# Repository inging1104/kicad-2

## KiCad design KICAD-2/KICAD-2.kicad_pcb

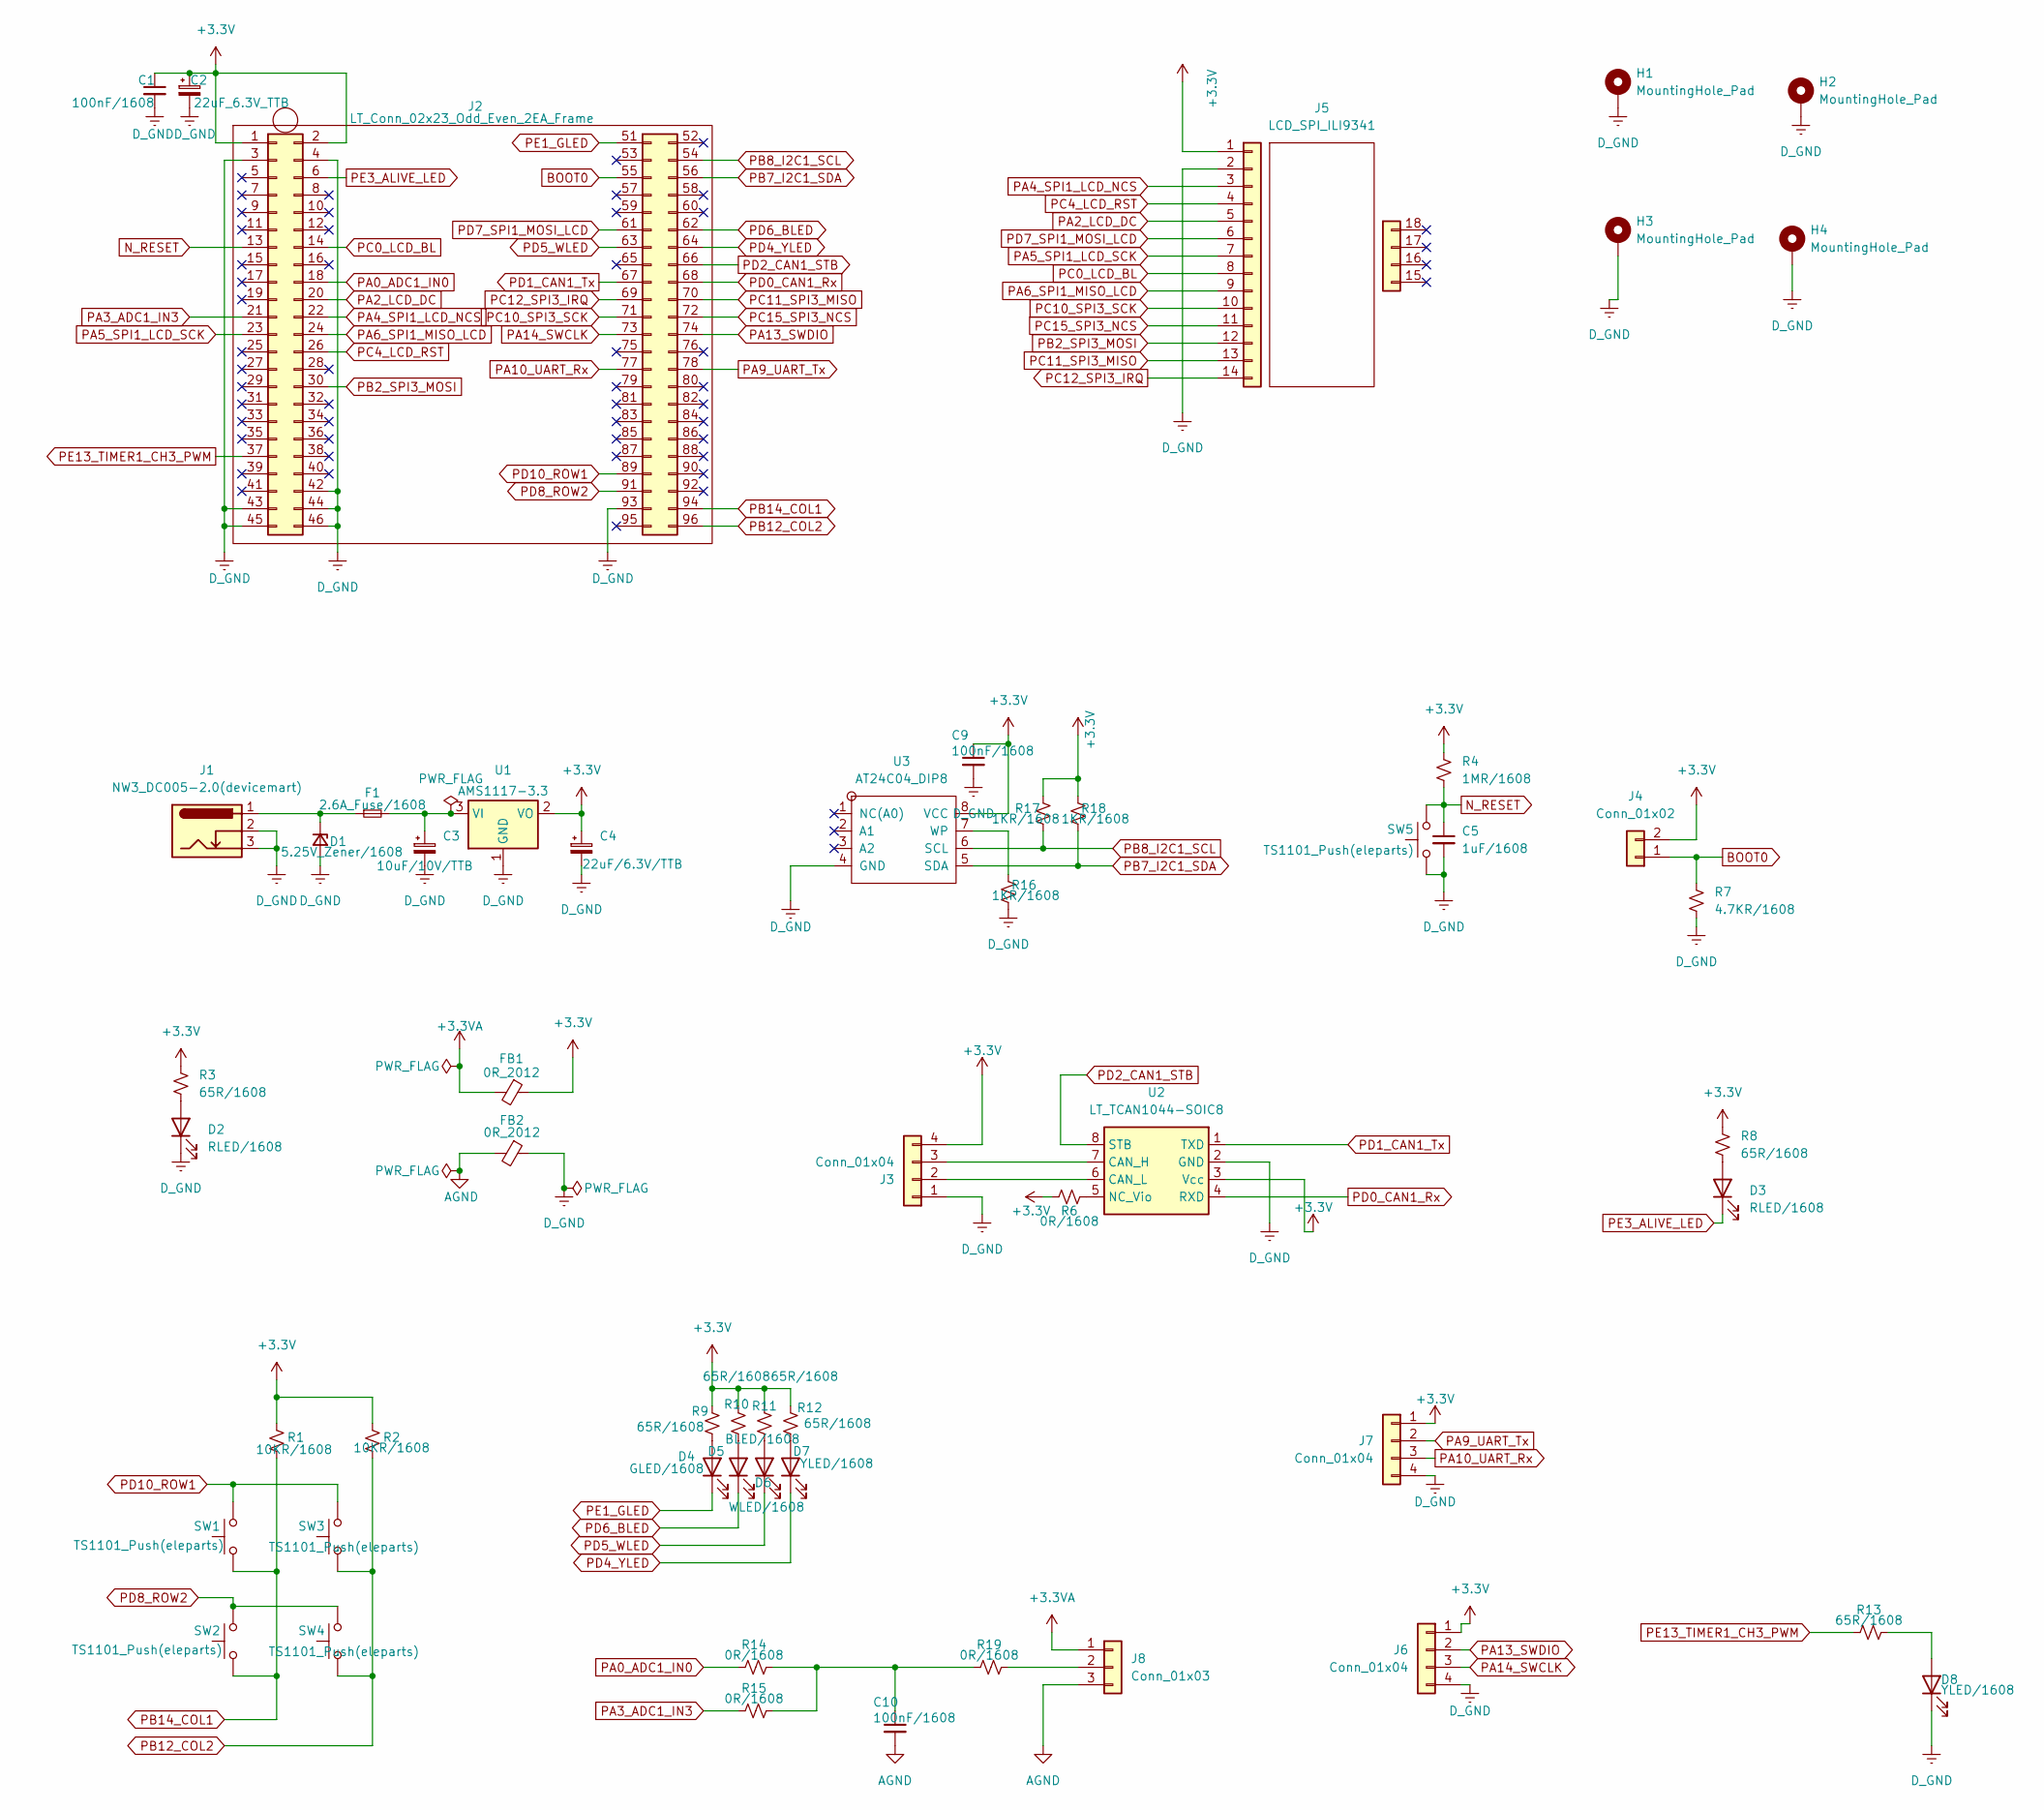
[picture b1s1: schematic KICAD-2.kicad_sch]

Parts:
C1, C9, C10: 100nF/1608; C_0603_1608Metric_Pad1.08x0.95mm_HandSolder
C2: 22uF_6.3V_TTB; CP_EIA-3528-21_Kemet-B_Pad1.50x2.35mm_HandSolder
C3: 10uF/10V/TTB; CP_EIA-3528-21_Kemet-B_Pad1.50x2.35mm_HandSolder
C4: 22uF/6.3V/TTB; CP_EIA-3528-21_Kemet-B_Pad1.50x2.35mm_HandSolder
C5: 1uF/1608; C_0603_1608Metric_Pad1.08x0.95mm_HandSolder
D1: 5.25V_Zener/1608; D_0603_1608Metric_Pad1.05x0.95mm_HandSolder
D2, D3: RLED/1608; LED_0603_1608Metric_Pad1.05x0.95mm_HandSolder
D4: GLED/1608; LED_0603_1608Metric_Pad1.05x0.95mm_HandSolder
D5: BLED/1608; LED_0603_1608Metric_Pad1.05x0.95mm_HandSolder
D6: WLED/1608; LED_0603_1608Metric_Pad1.05x0.95mm_HandSolder
D7, D8: YLED/1608; LED_0603_1608Metric_Pad1.05x0.95mm_HandSolder
F1: 2.6A_Fuse/1608; Fuse_0603_1608Metric_Pad1.05x0.95mm_HandSolder
FB1, FB2: 0R_2012; R_0805_2012Metric_Pad1.20x1.40mm_HandSolder
H1, H2, H3, H4: MountingHole_Pad; LT_MountingHole_3.2mm_M3_Pad_TopBottom
J1: NW3_DC005-2.0(devicemart); BarrelJack_GCT_DCJ200-10-A_Horizontal
J2: LT_Conn_02x23_Odd_Even_2EA_Frame; LT_STM32F767VGT-23x2_Frame
J3, J6, J7: Conn_01x04; PinHeader_1x04_P2.54mm_Vertical
J4: Conn_01x02; PinHeader_1x02_P2.54mm_Vertical
J5: LCD_SPI_ILI9341; LT_LCD_SPI_ILI9341_P2.54mm
J8: Conn_01x03; PinHeader_1x03_P2.54mm_Vertical
R1, R2: 10KR/1608; R_0603_1608Metric_Pad0.98x0.95mm_HandSolder
R3, R8, R9, R10, R11, R12, R13: 65R/1608; R_0603_1608Metric_Pad0.98x0.95mm_HandSolder
R4: 1MR/1608; R_0603_1608Metric_Pad0.98x0.95mm_HandSolder
R6, R14, R15, R19: 0R/1608; R_0603_1608Metric_Pad0.98x0.95mm_HandSolder
R7: 4.7KR/1608; R_0603_1608Metric_Pad0.98x0.95mm_HandSolder
R16, R17, R18: 1KR/1608; R_0603_1608Metric_Pad0.98x0.95mm_HandSolder
SW1, SW2, SW3, SW4, SW5: TS1101_Push(eleparts); LT_TS-1101_SW
U1: AMS1117-3.3; SOT-223-3_TabPin2
U2: LT_TCAN1044-SOIC8; LT_SOIC-8_3.9x4.9mm_P1.27mm
U3: AT24C04_DIP8; LT_DIP-8_W7.62mm_Socket

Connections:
+3.3V: C1.1, C2.1, C4.1, C9.1, FB1.1, J2.1, J2.2, J3.4, J4.2, J5.1, J6.1, J7.1, R1.1, R2.1, R3.2, R4.2, R6.2, R8.2, R9.1, R10.1, R11.1, R12.1, R17.1, R18.1, U1.2 (VO), U2.3 (Vcc), U3.8 (VCC)
+3.3VA: FB1.2, J8.1
AGND: C10.2, FB2.2, J8.3
BOOT0: J2.55, J4.1, R7.2
D_GND: C1.2, C2.2, C3.2, C4.2, C5.2, C9.2, D1.2 (A), D2.1 (K), D8.1 (K), FB2.1, H1.1, H2.1, H3.1, H4.1, J1.2, J1.3, J2.3, J2.4, J2.42, J2.43, J2.44, J2.45, J2.46, J2.93, J3.1, J5.2, J6.4, J7.4, R7.1, R16.2, SW5.1, U1.1 (GND), U2.2 (GND), U3.4 (GND)
N_RESET: C5.1, J2.13, R4.1, SW5.2
unnamed: C10.1, R14.2, R15.2, R19.1
unnamed: D1.1 (K), F1.1, J1.1
unnamed: D2.2 (A), R3.1
unnamed: D3.2 (A), R8.1
unnamed: D4.2 (A), R9.2
unnamed: D5.2 (A), R10.2
unnamed: D6.2 (A), R11.2
unnamed: D7.2 (A), R12.2
unnamed: D8.2 (A), R13.2
unnamed: J3.2, U2.6 (CAN_L)
unnamed: J3.3, U2.7 (CAN_H)
unnamed: J8.2, R19.2
unnamed: C3.1, F1.2, U1.3 (VI)
unnamed: R6.1, U2.5 (NC_Vio)
unnamed: R16.1, U3.7 (WP)
PA0_ADC1_IN0: J2.18, R14.1
PA2_LCD_DC: J2.20, J5.5
PA3_ADC1_IN3: J2.21, R15.1
PA4_SPI1_LCD_NCS: J2.22, J5.3
PA5_SPI1_LCD_SCK: J2.23, J5.7
PA6_SPI1_MISO_LCD: J2.24, J5.9
PA9_UART_Tx: J2.78, J7.2
PA10_UART_Rx: J2.77, J7.3
PA13_SWDIO: J2.74, J6.2
PA14_SWCLK: J2.73, J6.3
PB2_SPI3_MOSI: J2.30, J5.12
PB7_I2C1_SDA: J2.56, R18.2, U3.5 (SDA)
PB8_I2C1_SCL: J2.54, R17.2, U3.6 (SCL)
PB12_COL2: J2.96, R2.2, SW3.1, SW4.1
PB14_COL1: J2.94, R1.2, SW1.1, SW2.1
PC0_LCD_BL: J2.14, J5.8
PC4_LCD_RST: J2.26, J5.4
PC10_SPI3_SCK: J2.71, J5.10
PC11_SPI3_MISO: J2.70, J5.13
PC12_SPI3_IRQ: J2.69, J5.14
PC15_SPI3_NCS: J2.72, J5.11
PD0_CAN1_Rx: J2.68, U2.4 (RXD)
PD1_CAN1_Tx: J2.67 (Pin_17), U2.1 (TXD)
PD2_CAN1_STB: J2.66, U2.8 (STB)
PD4_YLED: D7.1 (K), J2.64
PD5_WLED: D6.1 (K), J2.63
PD6_BLED: D5.1 (K), J2.62 (Pin_12)
PD7_SPI1_MOSI_LCD: J2.61, J5.6
PD8_ROW2: J2.91, SW2.2, SW4.2
PD10_ROW1: J2.89, SW1.2, SW3.2
PE1_GLED: D4.1 (K), J2.51
PE3_ALIVE_LED: D3.1 (K), J2.6
PE13_TIMER1_CH3_PWM: J2.37, R13.1

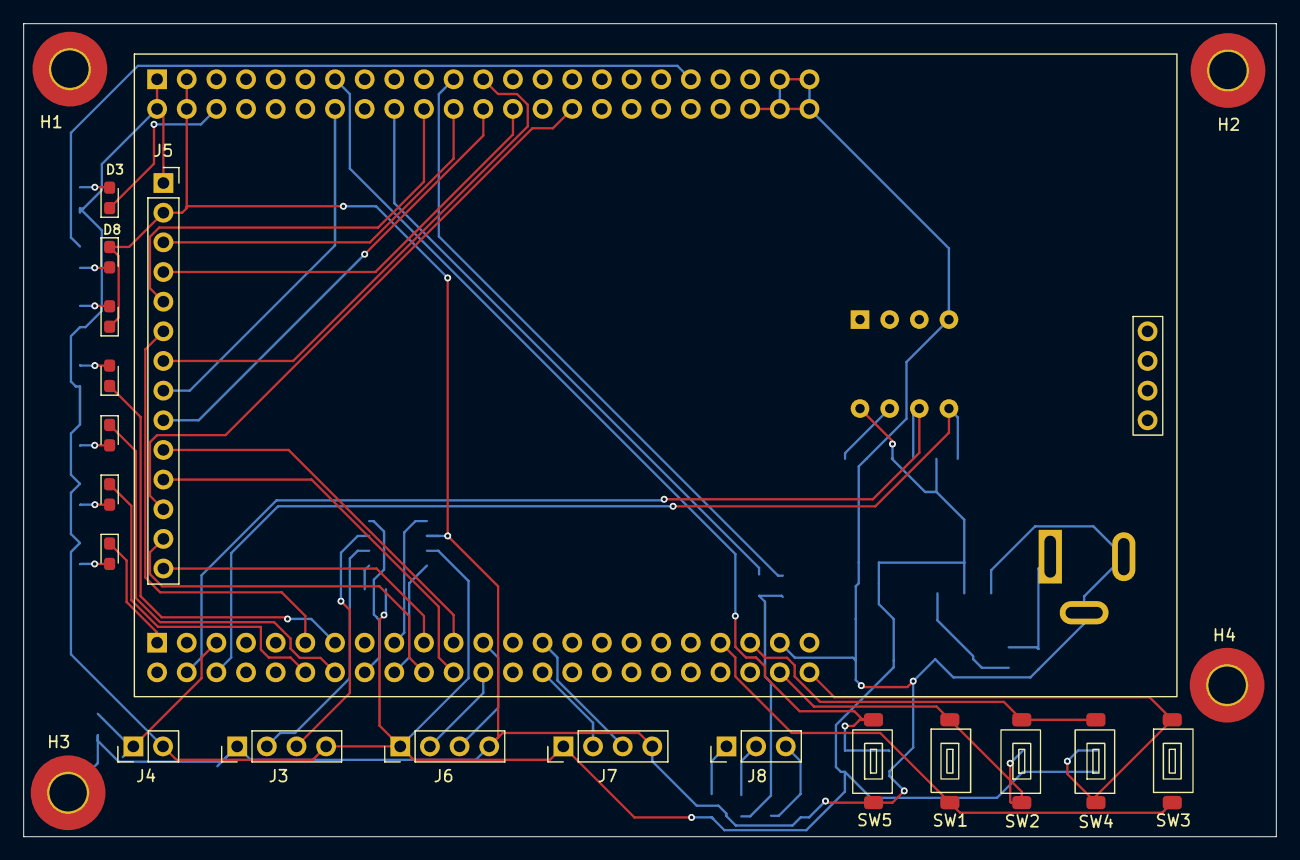
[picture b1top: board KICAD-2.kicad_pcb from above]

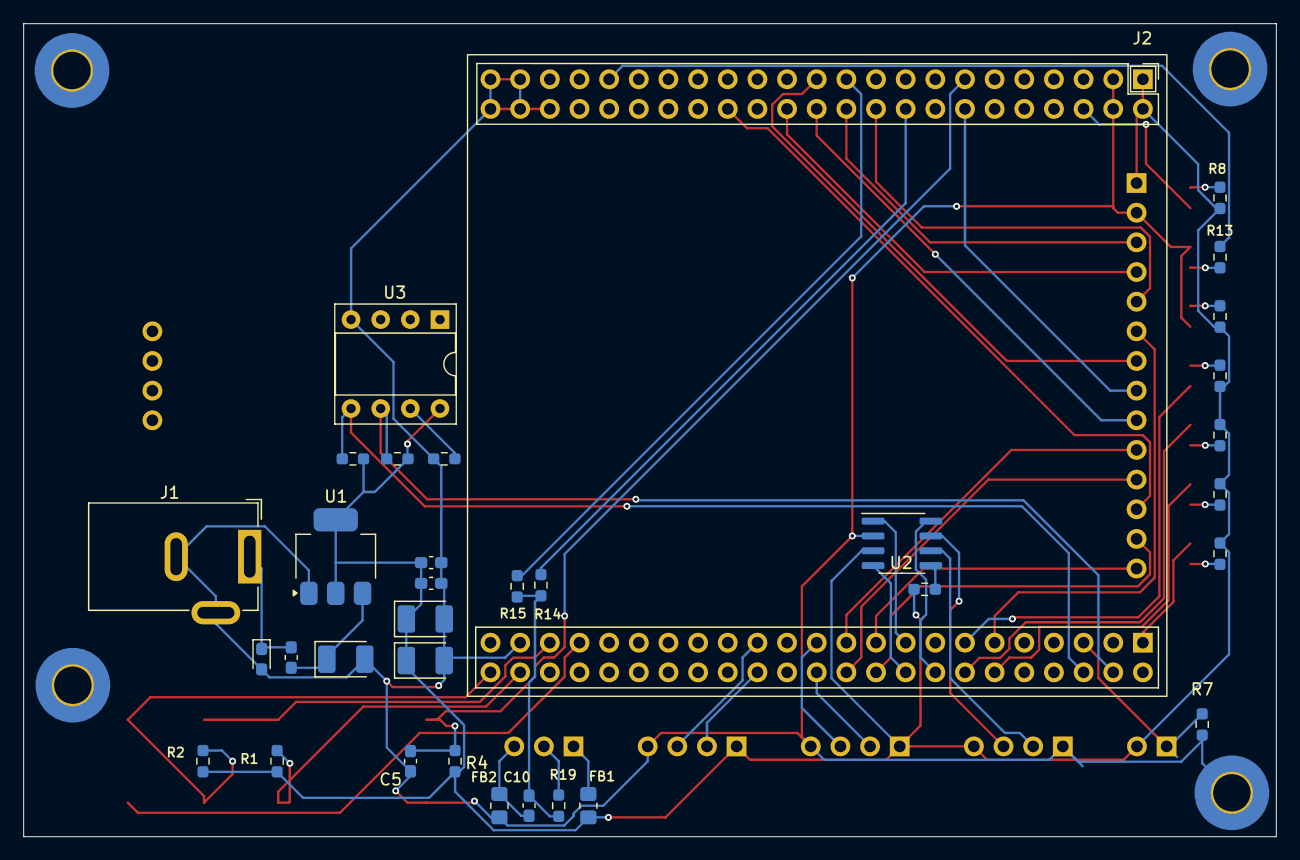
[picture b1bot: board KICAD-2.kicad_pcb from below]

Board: 2 copper layers, 107.3 x 69.6 mm, 56 parts (34 on the bottom side), 54 nets.

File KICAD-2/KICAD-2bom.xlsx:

Reference | Value | Qty | Unit Price(\) | Amount(\) | Maker | Vendor | Delivery | Remark
C1,C9,C10 | 100nF/1608 | 3 | 5 | 15 | SS | E-mart | 10 | 특이사항
C2 | 22uF_6.3V_TTB | 1 |  | 1
C3 | 10uF/10V/TTB | 1
C4 | 22uF/6.3V/TTB | 1
C5 | 1uF/1608 | 1
D1 | 5.25V_Zener/1608 | 1
D2,D3 | RLED/1608 | 2
D4 | GLED/1608 | 1
D5 | BLED/1608 | 1
D6 | WLED/1608 | 1
D7,D8 | YLED/1608 | 2
F1 | 2.6A_Fuse/1608 | 1
FB1,FB2 | 0R_2012 | 2
J1 | NW3_DC005-2.0(devicemart) | 1
J2 | LT_Conn_02x23_Odd_Even_2EA_Frame | 1
J3,J6,J7 | Conn_01x04 | 3
J4 | Conn_01x02 | 1
J5 | LCD_SPI_ILI9341 | 1
J8 | Conn_01x03 | 1
R1,R2 | 10KR/1608 | 2
R3,R8,R9,R10,R11,R12,R13 | 65R/1608 | 7
R4 | 1MR/1608 | 1
R6,R14,R15,R19 | 0R/1608 | 4
R7 | 4.7KR/1608 | 1
R16,R17,R18 | 1KR/1608 | 3
SW1,SW2,SW3,SW4,SW5 | TS1101_Push(eleparts) | 5
U1 | AMS1117-3.3 | 1
U2 | LT_TCAN1044-SOIC8 | 1
U3 | AT24C04_DIP8 | 1
